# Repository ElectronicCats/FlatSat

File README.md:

# Flatsat 

<p align="center">
    <a href="https://github.com/ElectronicCats/FlatSat/wiki">
        <img src="https://private-user-images.githubusercontent.com/107638696/595693319-c0883c17-046c-4819-b3c2-2ec70a0c5052.png?jwt=eyJ0eXAiOiJKV1QiLCJhbGciOiJIUzI1NiJ9.eyJpc3MiOiJnaXRodWIuY29tIiwiYXVkIjoicmF3LmdpdGh1YnVzZXJjb250ZW50LmNvbSIsImtleSI6ImtleTUiLCJleHAiOjE3OTEyMzc0NjYsIm5iZiI6MTc5MTIzNzE2NiwicGF0aCI6Ii8xMDc2Mzg2OTYvNTk1NjkzMzE5LWMwODgzYzE3LTA0NmMtNDgxOS1iM2MyLTJlYzcwYTBjNTA1Mi5wbmc_WC1BbXotQWxnb3JpdGhtPUFXUzQtSE1BQy1TSEEyNTYmWC1BbXotQ3JlZGVudGlhbD1BS0lBVkNPRFlMU0E1M1BRSzRaQSUyRjIwMjYxMDA1JTJGdXMtZWFzdC0xJTJGczMlMkZhd3M0X3JlcXVlc3QmWC1BbXotRGF0ZT0yMDI2MTAwNVQyMTUyNDZaJlgtQW16LUV4cGlyZXM9MzAwJlgtQW16LVNpZ25hdHVyZT0wM2RjYmU0NjI5OGJjNTY4YjhhNTAxMzIxZWE2ZTU4NDdjMzZmOTUyMDU1MGM0ODgwMjBiM2Y4Zjc5MjgxMDYzJlgtQW16LVNpZ25lZEhlYWRlcnM9aG9zdCZyZXNwb25zZS1jb250ZW50LXR5cGU9aW1hZ2UlMkZwbmcifQ.afATuDfkrx6oh0gf8nJ7T6D2viSOg3LT_uPS4Qk82Y4" width=70%>
    </a>
</p>

<p align=center>

</p>

Flatsat is a hardware based training platform designed to be vulnerable on purpose. It’s built for hackers, engineers, and space enthusiasts who want to dive deep into space-grade systems, learn cybersecurity concepts, and prototype their own payloads.

Flatsat is designed to help you learn and prototype radio systems safely and legally, all while gaining real-world skills in RF communication, signal analysis, and protocol fuzzing.

## What You Can Do With Flatsat
- **Hands-on Learning:** Use Flatsat as the hardware companion to the [**PwnSat**](https://pwnsat.org/) course, with structured lessons on binary exploitation, secure communication, reverse engineering, and space protocols.
- **Hack Real Vulnerabilities:**  Explore and exploit firmware designed to simulate real-world satellite systems and vulnerabilities. It’s a safe playground for learning and discovery.
- **Join the Mission CTF:**  Participate in space-themed capture-the-flag challenges that simulate real satellite operation scenarios.
- **Prototype Your Payloads:**  Use the onboard components to develop and test your own payload logic, radio communication, or telemetry systems before launching bigger projects.

> [!IMPORTANT]
> **This project was created for educational purposes, to teach and learn aerospace cybersecurity. Neither PWNSAT nor Electronic Cats are responsible for how the knowledge, code, or tools hosted in the official repository are used. Use only against hardware, firmware, or signal sources you own or are explicitly authorized to test.**
> 
> Flatsat uses ISM (Industrial, Scientific, and Medical) band frequencies for all RF communication,  typically 433 MHz or 915 MHz, depending on your region. These frequencies are internationally reserved for unlicensed, experimental, and educational use.
>
> This ensures that Flatsat does not interfere with any production space systems, licensed satellites, or critical ground infrastructure.

## Hardware Infrastructure

The infrastructure is designed for **FlatSat** testing, where hardware components are laid out for accessibility and auditing.

| **Component** | **Description**           | **Interface**            |
| ------------- | ------------------------- | ------------------------ |
| **MCU**       | Raspberry Pi RP2040       | Dual Core ARM Cortex-M0+ |
| **Radio 0**   | SX1262 LoRa (Uplink)      | SPI0 / NSS Pin 17        |
| **Radio 1**   | SX1262 LoRa (Downlink)    | SPI0 / NSS Pin 5         |
| **IMU**       | LIS2DH12 Accelerometer    | I2C (SDA 20, SCL 21)     |
| **ENV**       | BME280 Environment Sensor | I2C (SDA 20, SCL 21)     |
| **Status**    | WS2812B NeoPixel          | GPIO 15                  |

##  FlatSat Firmware

The firmware splits tasks across two cores, the system ensures that high-speed data links do not interfere with time-critical radio operations.

The firmware is located in a different repository: https://github.com/ElectronicCats/flatsat-ground-station

The core of the communication system is the [**CCSDS Space Packet Protocol**](https://ccsds.org/Pubs/133x0b2e2.pdf). This allows the spacecraft to route data using **Application Process Identifiers (APIDs)**, enabling modular subsystem addressing.

Modern satellites are no longer isolated systems; they are software-defined assets. The vulnerabilities identified in this firmware mirror historical "anomalies" and documented attacks on orbiting infrastructure.

Since the firmware lacks a Cryptographic Authentication layer, the system is vulnerable to **Command Spoofing**.

An attacker uses a Software Defined Radio (SDR) to capture a legitimate "Telemetry" packet to identify the `SPACECRAFT_ID` and the current `Sequence Count`.
  
This happened in the real world. In 1998, the **ROSAT** (Röntgen Satellite) was allegedly compromised via a ground station breach, where attackers sent commands to point the solar panels directly at the sun, eventually frying the batteries. While that was a network breach, the lack of authentication on the RF link makes this firmware susceptible to the same outcome.

## Technical Documentation and Guides (Wiki)

All deep technical documentation, source analysis, and setup guides have been centralized. If you want to start debugging, or exploiting the platform, please visit the [FlatSat Wiki](https://github.com/ElectronicCats/FlatSat/wiki). The information from the Pwnsat repository has been included in our wiki.

## How to contribute 

[pwnsat.org](https://pwnsat.org/) and [flatsat.org](https://flatsat.org/)
Contributions are welcome!

Please read the document [**Contribution manual**](https://github.com/ElectronicCats/electroniccats-cla/blob/main/electroniccats-contribution-manual.md) which will show you how to contribute your changes to the project.

✨ Thanks to all our [Contributors](https://github.com/ElectronicCats/Flatsat/graphs/contributors)! ✨

See [**_Electronic Cats CLA_**](https://github.com/ElectronicCats/electroniccats-cla/blob/main/electroniccats-cla.md) for more information.

See the [**Community code of conduct**](https://github.com/ElectronicCats/electroniccats-cla/blob/main/electroniccats-community-code-of-conduct.md) for a vision of the community we want to build and what we expect from it.

## License

Electronic Cats invests time and resources providing this open source design, please support Electronic Cats and open-source hardware by purchasing products from Electronic Cats!

Designed by Electronic Cats and PWNSAT.

Hardware released under an CERN Open Hardware Licence v1.2. See the LICENSE_HARDWARE file for more information.

Electronic Cats and PWNSAT is a registered trademark, please do not use if you sell these PCBs.

## Special Thanks
A special thanks to **Alex Lynd**. His support made it possible to kick off the first version of the project, and his contribution remains a fundamental part of PwnSat. His work will always be embedded in what this project has become.

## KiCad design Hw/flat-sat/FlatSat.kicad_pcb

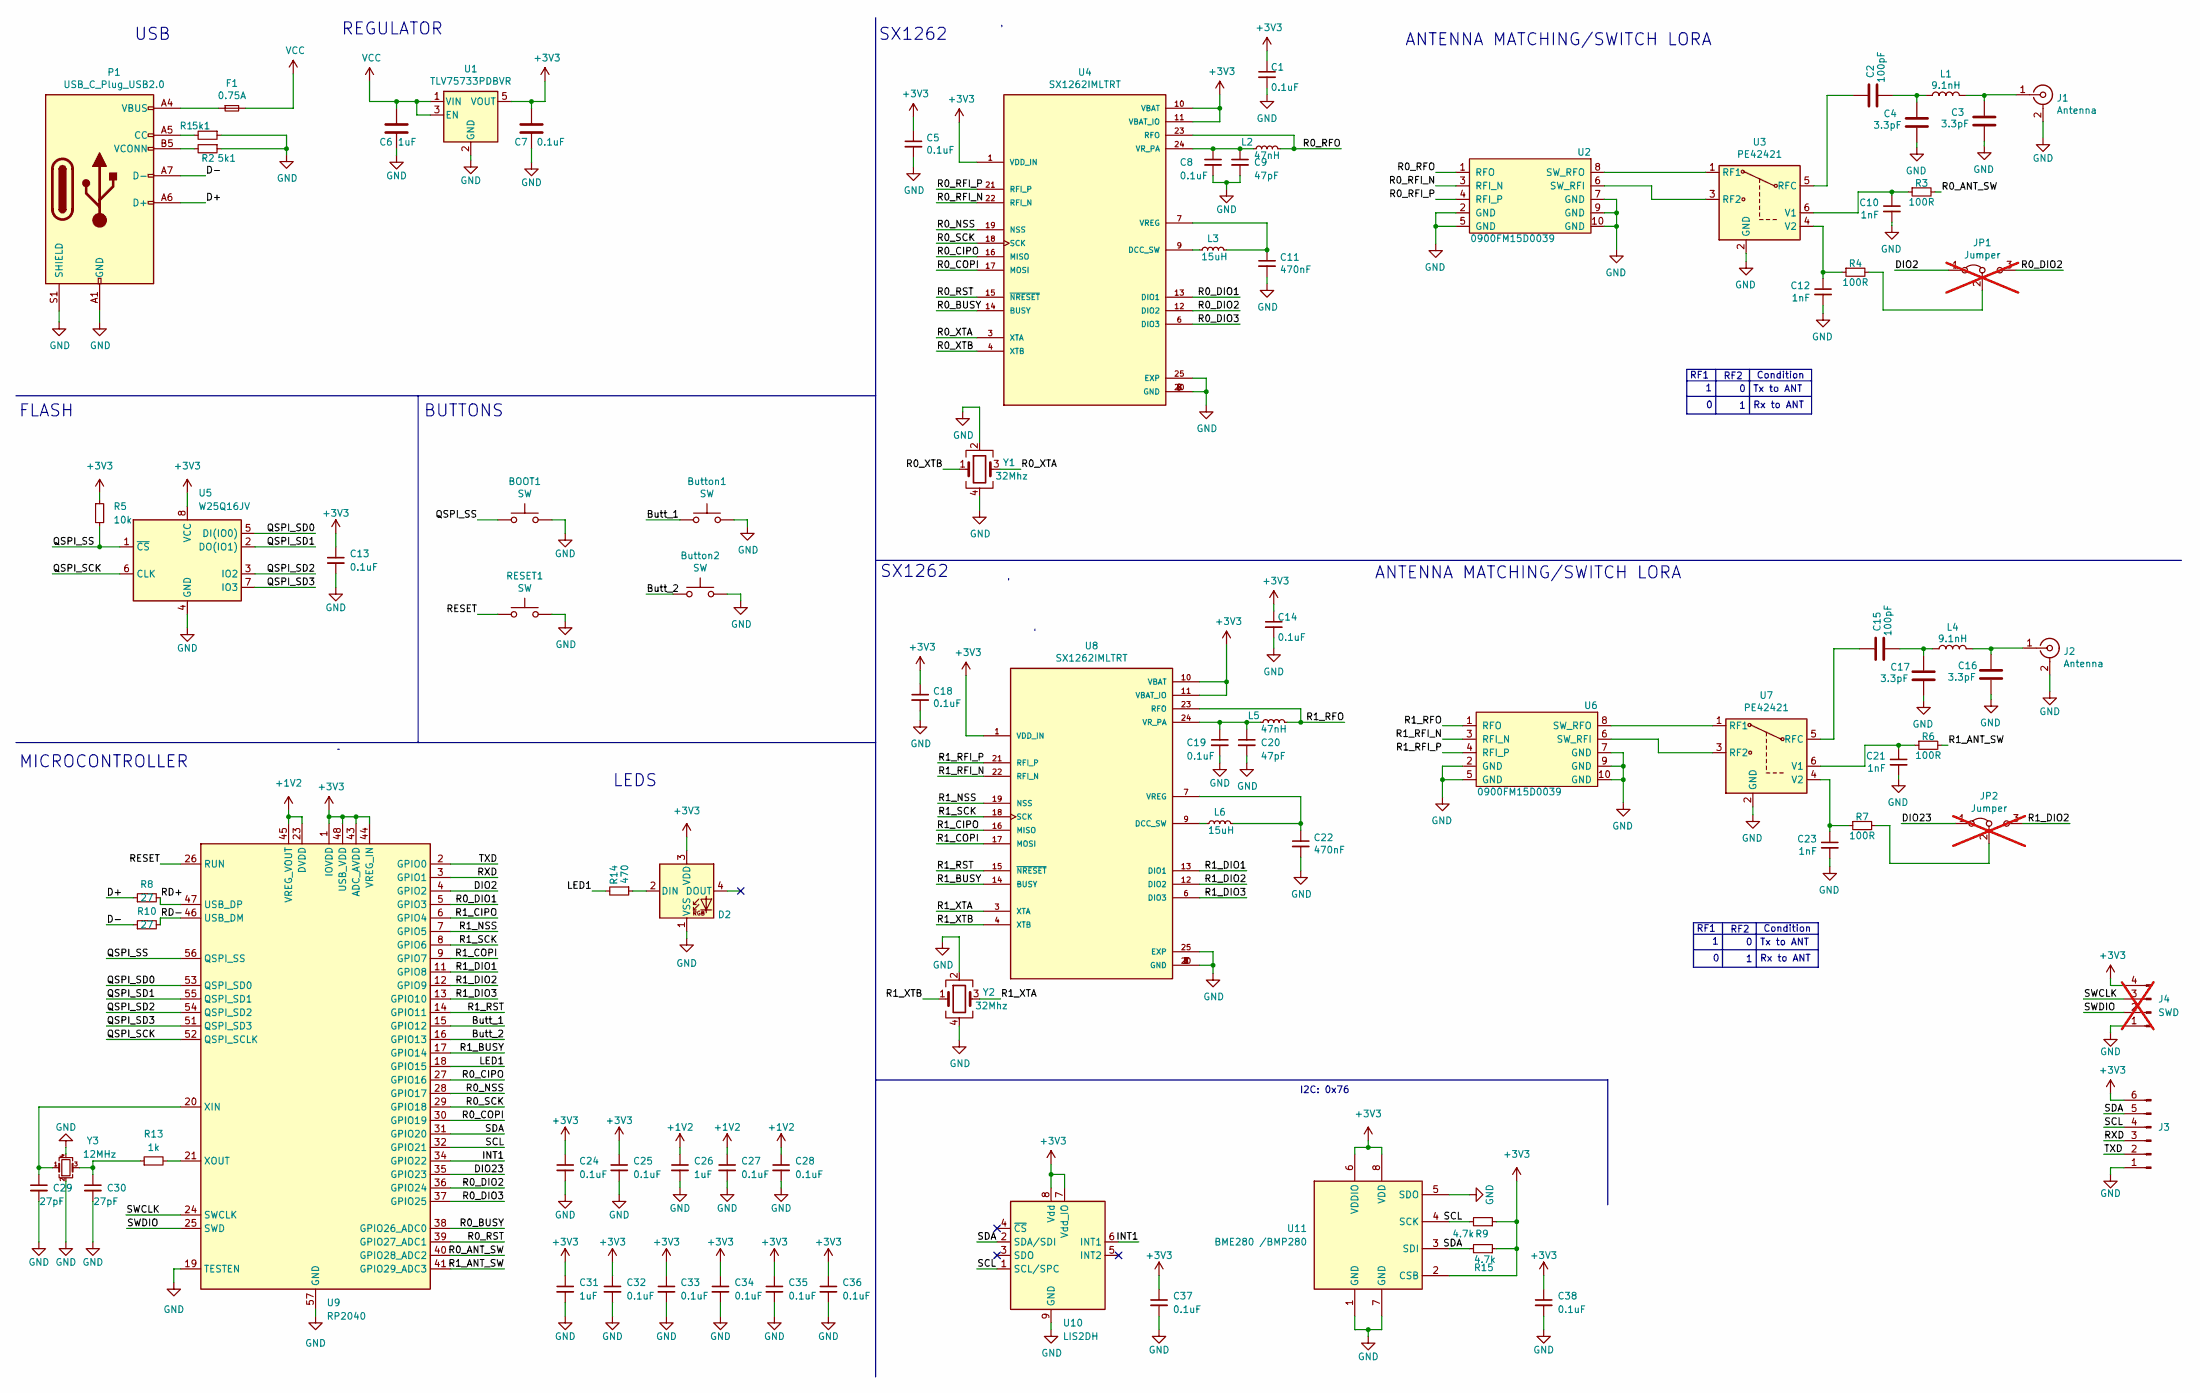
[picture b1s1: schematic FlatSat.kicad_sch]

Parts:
BOOT1: SW; TS1088R02026; LCSC# C455281
Button1, Button2: SW; TS1088R02026; LCSC# C455281
C1, C5, C7, C8, C13, C14, C18, C19, C24, C25, C27, C28, C32, C33, C34, C35, C36, C37, C38: 0.1uF; C_0402_1005Metric; LCSC# C56392
C2, C15: 100pF; C_0402_1005Metric; LCSC# C541374
C3, C4, C16, C17: 3.3pF; C_0402_1005Metric; LCSC# C1565
C6, C26, C31: 1uF; C_0402_1005Metric; LCSC# C52923
C9, C20: 47pF; C_0402_1005Metric; LCSC# C437519
C10, C12, C21, C23: 1nF; C_0402_1005Metric; LCSC# C335530
C11, C22: 470nF; C_0402_1005Metric; LCSC# C47339
C29, C30: 27pF; C_0402_1005Metric; Mouser# 81-GJM1555C1H270FB1D; LCSC# C424826
D2: SK6812MINI; SK6812MINI-HS; LCSC# C2922787
F1: 0.75A; Fuse_0603_1608Metric_Pad1.05x0.95mm_HandSolder; Mouser# 594-MFU0805FF00500P1
J1, J2: Antenna; SMA_EDGE; LCSC# C530661
J3: periphs; PinHeader_1x06_P2.54mm_Vertical
J4: SWD; PinHeader_1x04_P2.54mm_Vertical; not fitted
JP1, JP2: Jumper; SolderJumper-3_P1.3mm_Bridged12_RoundedPad1.0x1.5mm_NumberL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; not fitted
L1, L4: 9.1nH; L_0603_1608Metric; LCSC# C395094
L2, L5: 47nH; L_0603_1608Metric; LCSC# C578001
L3, L6: 15uH; L_0603_1608Metric; LCSC# C57838
P1: USB_C_Plug_USB2.0; C393939; LCSC# C709357
R1, R2: 5k1; R_0402_1005Metric; LCSC# C25905
R3, R4, R6, R7: 100R; R_0402_1005Metric; LCSC# C25076
R5: 10k; R_0402_1005Metric; Mouser# 594-MCS04020D1002BE0; LCSC# C25531
R8, R10: 27; R_0402_1005Metric; Mouser# 755-ESR01MZPF27R0; LCSC# C25100
R9, R15: 4.7k; R_0402_1005Metric; Mouser# 594-MCS04020D1002BE0; LCSC# C25900
R13: 1k; R_0402_1005Metric; Mouser# 594-MCS0402MD1001DE0; LCSC# C11702
R14: 470; R_0402_1005Metric; LCSC# C25117
RESET1: SW; TS1088R02026; LCSC# C455281
U1: TLV75733PDBVR; SOT-23-5; LCSC# C485517
U2, U6: 0900FM15D0039; 0900FM15D0039E; Mouser# 609-0900FM15D0039E
U3, U7: PE42421; SOT-363_SC-70-6; Mouser# 81-PE42421SCAA-Z; LCSC# C470893
U4, U8: SX1262IMLTRT; QFN-24-1EP_4x4mm_P0.5mm_EP2.65x2.65mm; Mouser# 947-SX1262IMLTRT
U5: W25Q16JV; Winbond_USON-8-2EP_3x4mm_P0.8mm_EP0.2x0.8mm; Mouser# 454-W25Q16JVUUIQTR
U9: RP2040; QFN-56-1EP_7x7mm_P0.4mm_EP3.2x3.2mm; LCSC# C2040
U10: LIS2DH; LGA-14_2x2mm_P0.35mm_LayoutBorder3x4y; LCSC# C155670
U11: BME280 /BMP280; Bosch_LGA-8_2.5x2.5mm_P0.65mm_ClockwisePinNumbering; LCSC# C92489
Y1, Y2: 32Mhz; Crystal_SMD_2520-4Pin_2.5x2.0mm; LCSC# C255969
Y3: 12MHz; Crystal_SMD_3225-4Pin_3.2x2.5mm; LCSC# C2848217

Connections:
+1V2: C26.1, C27.1, C28.1, U9.23 (DVDD), U9.45 (VREG_VOUT), U9.50 (DVDD)
+3V3: C1.1, C5.1, C7.2, C13.1, C14.1, C18.1, C24.1, C25.1, C31.1, C32.1, C33.1, C34.1, C35.1, C36.1, C37.1, C38.1, D2.3 (VDD), J3.6, J4.4, R5.1, R9.1, R15.1, U1.5 (VOUT), U4.1 (VDD_IN), U4.10 (VBAT), U4.11 (VBAT_IO), U5.8 (VCC), U8.1 (VDD_IN), U8.10 (VBAT), U8.11 (VBAT_IO), U9.1 (IOVDD), U9.10 (IOVDD), U9.22 (IOVDD), U9.33 (IOVDD), U9.42 (IOVDD), U9.43 (ADC_AVDD), U9.44 (VREG_IN), U9.48 (USB_VDD), U9.49 (IOVDD), U10.7 (Vdd_IO), U10.8 (Vdd), U11.2 (CSB), U11.6 (VDDIO), U11.8 (VDD)
/Butt_1: Button1.1, U9.15 (GPIO12)
/Butt_2: Button2.1, U9.16 (GPIO13)
/D+: P1.A6 (D+), R8.1
/D-: P1.A7 (D-), R10.1
/DIO2: JP1.1 (A), U9.4 (GPIO2)
/DIO23: JP2.1 (A), U9.35 (GPIO23)
/INT1: U9.34 (GPIO22), U10.6 (INT1)
/LED1: R14.2, U9.18 (GPIO15)
/QSPI_SCK: U5.6 (CLK), U9.52 (QSPI_SCLK)
/QSPI_SD0: U5.5 (DI(IO0)), U9.53 (QSPI_SD0)
/QSPI_SD1: U5.2 (DO(IO1)), U9.55 (QSPI_SD1)
/QSPI_SD2: U5.3 (IO2), U9.54 (QSPI_SD2)
/QSPI_SD3: U5.7 (IO3), U9.51 (QSPI_SD3)
/QSPI_SS: BOOT1.1, R5.2, U5.1 (~CS), U9.56 (QSPI_SS)
/R0_ANT_SW: R3.2, U9.40 (GPIO28_ADC2)
/R0_BUSY: U4.14 (BUSY), U9.38 (GPIO26_ADC0)
/R0_CIPO: U4.16 (MISO), U9.27 (GPIO16)
/R0_COPI: U4.17 (MOSI), U9.30 (GPIO19)
/R0_DIO1: U4.13 (DIO1), U9.5 (GPIO3)
/R0_DIO2: JP1.3 (B), U4.12 (DIO2), U9.36 (GPIO24)
/R0_DIO3: U4.6 (DIO3), U9.37 (GPIO25)
/R0_NSS: U4.19 (NSS), U9.28 (GPIO17)
/R0_RFI_N: U2.3 (RFI_N), U4.22 (RFI_N)
/R0_RFI_P: U2.4 (RFI_P), U4.21 (RFI_P)
/R0_RFO: L2.2, U2.1 (RFO), U4.23 (RFO)
/R0_RST: U4.15 (~NRESET), U9.39 (GPIO27_ADC1)
/R0_SCK: U4.18 (SCK), U9.29 (GPIO18)
/R0_XTA: U4.3 (XTA), Y1.3
/R0_XTB: U4.4 (XTB), Y1.1
/R1_ANT_SW: R6.2, U9.41 (GPIO29_ADC3)
/R1_BUSY: U8.14 (BUSY), U9.17 (GPIO14)
/R1_CIPO: U8.16 (MISO), U9.6 (GPIO4)
/R1_COPI: U8.17 (MOSI), U9.9 (GPIO7)
/R1_DIO1: U8.13 (DIO1), U9.11 (GPIO8)
/R1_DIO2: JP2.3 (B), U8.12 (DIO2), U9.12 (GPIO9)
/R1_DIO3: U8.6 (DIO3), U9.13 (GPIO10)
/R1_NSS: U8.19 (NSS), U9.7 (GPIO5)
/R1_RFI_N: U6.3 (RFI_N), U8.22 (RFI_N)
/R1_RFI_P: U6.4 (RFI_P), U8.21 (RFI_P)
/R1_RFO: L5.2, U6.1 (RFO), U8.23 (RFO)
/R1_RST: U8.15 (~NRESET), U9.14 (GPIO11)
/R1_SCK: U8.18 (SCK), U9.8 (GPIO6)
/R1_XTA: U8.3 (XTA), Y2.3
/R1_XTB: U8.4 (XTB), Y2.1
/RD+: R8.2, U9.47 (USB_DP)
/RD-: R10.2, U9.46 (USB_DM)
/RESET: RESET1.1, U9.26 (RUN)
/RXD: J3.3, U9.3 (GPIO1)
/SCL: J3.4, R9.2, U9.32 (GPIO21), U10.1 (SCL/SPC), U11.4 (SCK)
/SDA: J3.5, R15.2, U9.31 (GPIO20), U10.2 (SDA/SDI), U11.3 (SDI)
/SWCLK: J4.3, U9.24 (SWCLK)
/SWDIO: J4.2, U9.25 (SWD)
/TXD: J3.2, U9.2 (GPIO0)
GND: BOOT1.2, Button1.2, Button2.2, C1.2, C3.2, C4.2, C5.2, C6.1, C7.1, C8.2, C9.2, C10.2, C11.2, C12.2, C13.2, C14.2, C16.2, C17.2, C18.2, C19.2, C20.2, C21.2, C22.2, C23.2, C24.2, C25.2, C26.2, C27.2, C28.2, C29.2, C30.2, C31.2, C32.2, C33.2, C34.2, C35.2, C36.2, C37.2, C38.2, D2.1 (VSS), J1.2 (Ext), J2.2 (Ext), J3.1, J4.1, P1.A1 (GND), P1.A12 (GND), P1.B1 (GND), P1.B12 (GND), P1.S1 (SHIELD), R1.1, R2.1, RESET1.2, U1.2 (GND), U2.2 (GND), U2.5 (GND), U2.7 (GND), U2.9 (GND), U2.10 (GND), U3.2 (GND), U4.2 (GND), U4.5 (GND), U4.8 (GND), U4.20 (GND), U4.25 (EXP), U5.4 (GND), U6.2 (GND), U6.5 (GND), U6.7 (GND), U6.9 (GND), U6.10 (GND), U7.2 (GND), U8.2 (GND), U8.5 (GND), U8.8 (GND), U8.20 (GND), U8.25 (EXP), U9.19 (TESTEN), U9.57 (GND), U10.9 (GND), U10.10 (GND), U10.11 (GND), U10.12 (GND), U10.13 (GND), U10.14 (GND), U11.1 (GND), U11.5 (SDO), U11.7 (GND), Y1.2, Y1.4, Y2.2, Y2.4, Y3.2, Y3.4
unnamed: C2.2, C4.1, L1.2
unnamed: C15.2, C17.1, L4.2
unnamed: C30.1, R13.1, Y3.3
unnamed: D2.2 (DIN), R14.1
unnamed: F1.1, P1.A4 (VBUS), P1.A9 (VBUS), P1.B4 (VBUS), P1.B9 (VBUS)
unnamed: C3.1, J1.1 (In), L1.1
unnamed: C16.1, J2.1 (In), L4.1
unnamed: JP1.2 (C), R4.2
unnamed: JP2.2 (C), R7.2
unnamed: P1.A5 (CC), R1.2
unnamed: P1.B5 (VCONN), R2.2
unnamed: U2.6 (SW_RFI), U3.3 (RF2)
unnamed: U2.8 (SW_RFO), U3.1 (RF1)
unnamed: C2.1, U3.5 (RFC)
unnamed: C10.1, R3.1, U3.6 (V1)
unnamed: C12.1, R4.1, U3.4 (V2)
unnamed: L3.1, U4.9 (DCC_SW)
unnamed: C11.1, L3.2, U4.7 (VREG)
unnamed: C8.1, C9.1, L2.1, U4.24 (VR_PA)
unnamed: U6.6 (SW_RFI), U7.3 (RF2)
unnamed: U6.8 (SW_RFO), U7.1 (RF1)
unnamed: C15.1, U7.5 (RFC)
unnamed: C21.1, R6.1, U7.6 (V1)
unnamed: C23.1, R7.1, U7.4 (V2)
unnamed: L6.1, U8.9 (DCC_SW)
unnamed: C22.1, L6.2, U8.7 (VREG)
unnamed: C19.1, C20.1, L5.1, U8.24 (VR_PA)
unnamed: C29.1, U9.20 (XIN), Y3.1
unnamed: R13.2, U9.21 (XOUT)
VCC: C6.2, F1.2, U1.1 (VIN), U1.3 (EN)

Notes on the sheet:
Rx to ANT
I2C: 0x76
Condition
REGULATOR
SX1262
ANTENNA MATCHING/SWITCH LORA
RF1
RF2
FLASH
Tx to ANT
BUTTONS
MICROCONTROLLER
USB
SX1262
LEDS

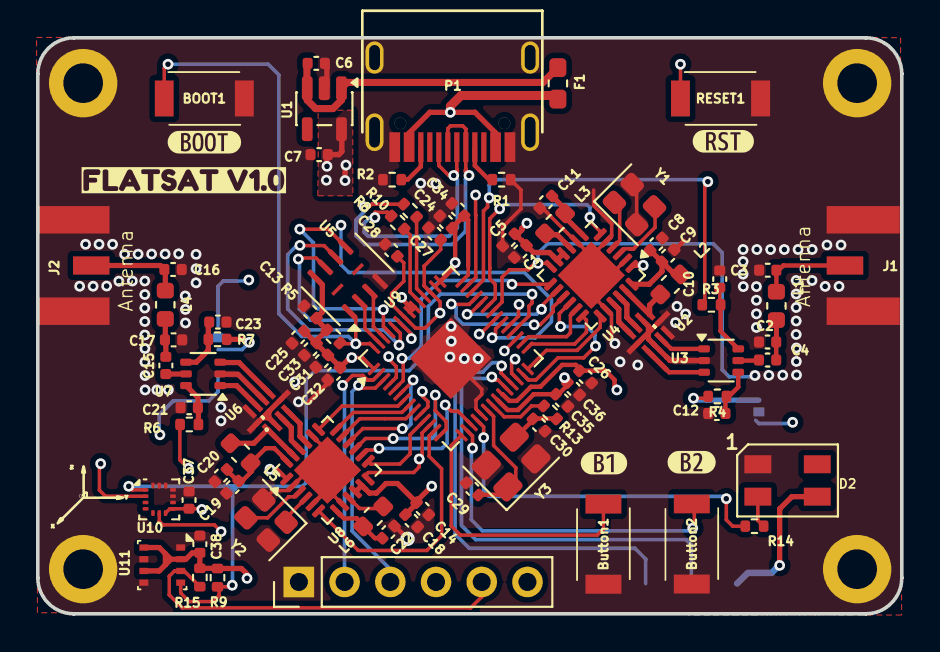
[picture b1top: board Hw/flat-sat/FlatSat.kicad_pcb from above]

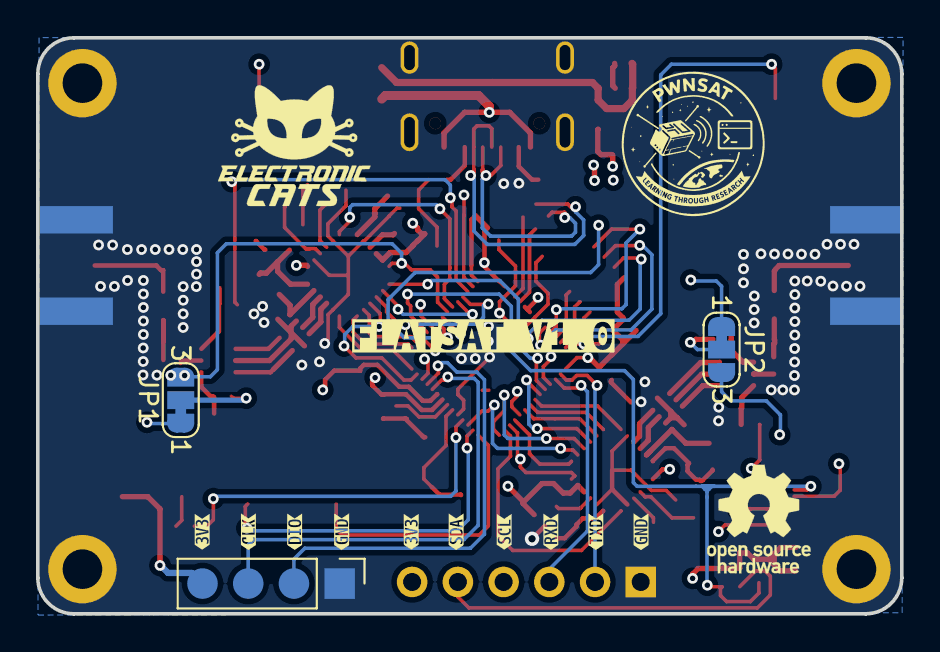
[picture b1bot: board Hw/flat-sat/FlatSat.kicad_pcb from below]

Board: 4 copper layers, 48.0 x 32.0 mm, 100 parts (14 on the bottom side), 86 nets.

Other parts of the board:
kibuzzard-696512BA, kibuzzard-696512BA#2: G***; kibuzzard-696512BA
kibuzzard-696512FB: G***; kibuzzard-696512FB
kibuzzard-6965130C: G***; kibuzzard-6965130C
kibuzzard-6965136B: G***; kibuzzard-6965136B
kibuzzard-69651236: G***; kibuzzard-69651236
kibuzzard-69651254: G***; kibuzzard-69651254
kibuzzard-69651304: G***; kibuzzard-69651304
kibuzzard-69651319: G***; kibuzzard-69651319
kibuzzard-69651321: G***; kibuzzard-69651321
kibuzzard-69651375: G***; kibuzzard-69651375
kibuzzard-69651380: G***; kibuzzard-69651380
kibuzzard-69652909: G***; kibuzzard-69652909
kibuzzard-69652922: G***; kibuzzard-69652922
kibuzzard-69652959: G***; kibuzzard-69652959
kibuzzard-69653048: G***; kibuzzard-69653048

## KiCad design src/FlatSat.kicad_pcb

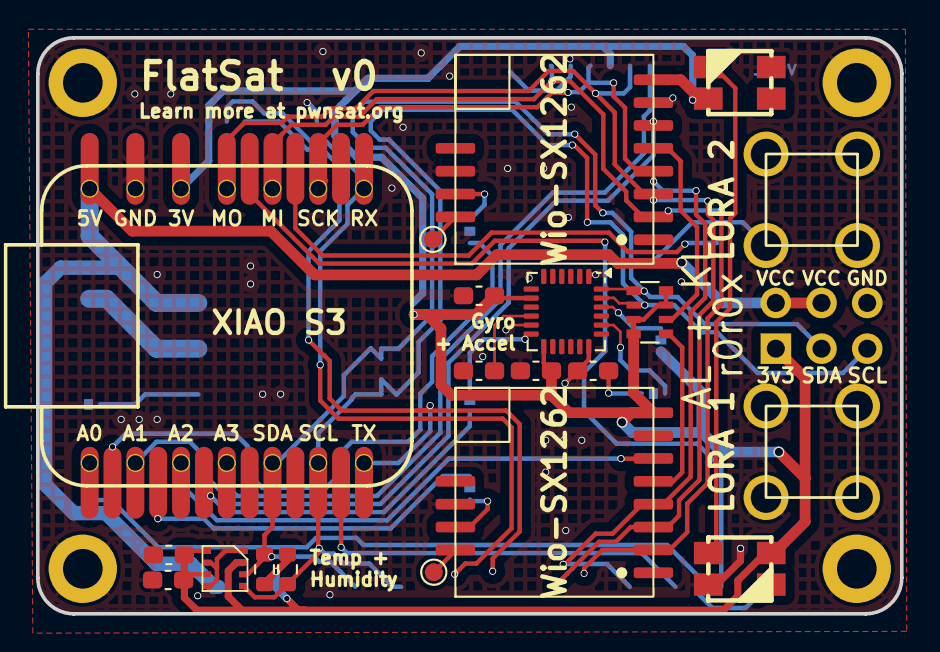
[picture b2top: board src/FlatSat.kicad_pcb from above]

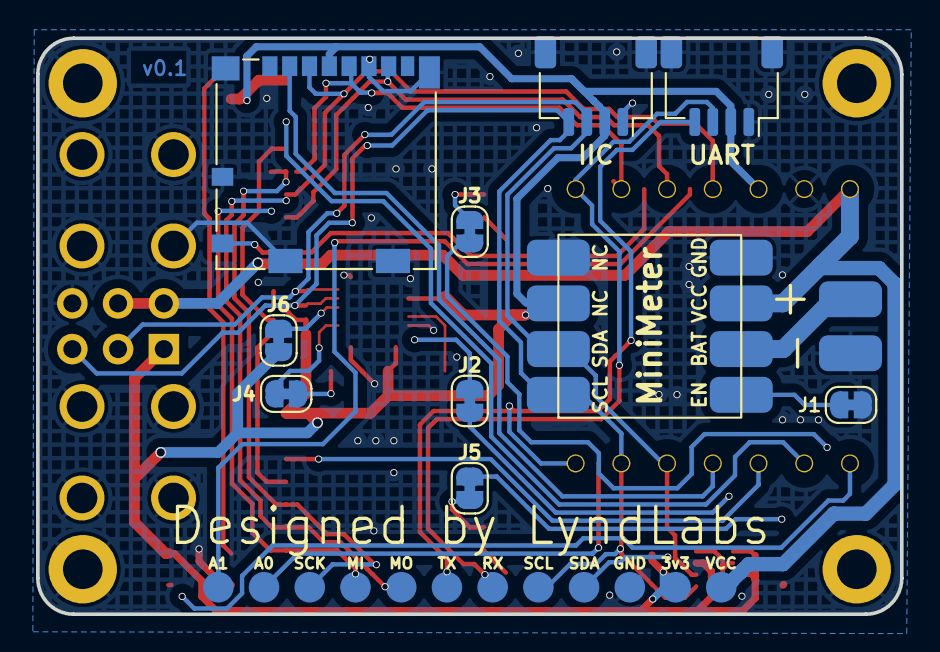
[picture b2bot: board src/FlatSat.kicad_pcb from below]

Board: 2 copper layers, 48.0 x 32.0 mm, 33 parts (12 on the bottom side), 34 nets.

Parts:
AE1, AE2: u.fl to SMA Edge Mount; SMA_Amphenol_901-143_Horizontal
C1, C4, C5: 0.1uf; C_0603_1608Metric_Pad1.08x0.95mm_HandSolder
C2: 2.2uf; C_0603_1608Metric_Pad1.08x0.95mm_HandSolder
C3, C6: 100nF; C_0603_1608Metric_Pad1.08x0.95mm_HandSolder
D1, D2: SK6812MINI; LED_SK6812MINI_PLCC4_3.5x3.5mm_P1.75mm
J1: LiPo; JST_PH_S2B-PH-SM4-TB_1x02-1MP_P2.00mm_Horizontal
J2, J3: Conn_01x04_MountingPin; JST_SH_SM04B-SRSS-TB_1x04-1MP_P1.00mm_Horizontal
J4: Conn_02x03_Odd_Even; PinHeader_2x03_P2.54mm_Vertical
J5: Conn_01x12_Pin; PinHeader_1x12_P2.54mm_Vertical
J7: Micro_SD_Card_Det2; microSD_HC_Molex_104031-0811
JP1, JP2, JP3, JP4, JP5, JP6: SolderJumper_2_Bridged; SolderJumper-2_P1.3mm_Bridged_RoundedPad1.0x1.5mm
R4, R5: 4.7K; R_0603_1608Metric
RN1: 10K; R_Array_Convex_4x0603
TP1, TP2: TestPoint; TestPoint_Pad_D1.0mm
U1: Xiao; XIAO_SMT
U2: MPU-6050 / 6500; InvenSense_QFN-24_4x4mm_P0.5mm
U3: BME280 /BMP280; Bosch_LGA-8_2.5x2.5mm_P0.65mm_ClockwisePinNumbering
U4: MiniMeter
U5, U6: Wio-SX1262

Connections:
+3V3: C3.1, C4.1, C5.1, C6.1, D1.4 (VDD), D2.4 (VDD), J2.2, J3.2, J4.1, J5.2, J7.4 (VDD), JP6.2 (B), R4.2, R5.1, RN1.3 (R3.1), RN1.4 (R4.1), RN1.7 (R2.2), RN1.8 (R1.2), U1.12 (3V3), U2.8 (VLOGIC), U2.13 (VDD), U3.2 (CSB), U3.6 (VDDIO), U3.8 (VDD), U4.2 (3V3), U5.8 (VCC), U6.8 (VCC)
A0: J5.11, U1.20 (D16)
A1: J5.12, U1.23 (D17)
BUSY1: JP3.2 (B), U1.15 (D11)
BUSY2: JP5.2 (B), U1.16 (D12)
CS1: U1.2 (D1), U5.6 (NSS)
CS2: U1.3 (D2), U6.6 (NSS)
GND: AE1.1, AE2.1, C1.2, C2.2, C3.2, C4.2, C5.2, C6.2, D1.2 (VSS), D2.2 (VSS), J1.1, J2.1, J2.MP (MountPin), J3.1, J3.MP (MountPin), J4.6, J5.3, J7.6 (VSS), J7.9 (DET_B), J7.11 (SHIELD), JP1.1 (A), U1.13 (GND), U2.1 (CLKIN), U2.11 (FSYNC), U2.18 (GND), U3.1 (GND), U3.5 (SDO), U3.7 (GND), U4.1 (GND), U4.5 (GND), U5.7 (GND), U5.10 (GND), U6.7 (GND), U6.10 (GND)
INT: JP2.2 (B), U1.17 (D13)
LED: D1.3 (DIN), U1.1 (D0)
MCU_RX: J2.3, J5.6, U1.8 (RX)
MCU_TX: J2.4, J5.7, U1.7 (TX)
MISO: J5.9, J7.7 (DAT0), U1.10 (MISO), U5.2 (MISO), U6.2 (MISO)
MOSI: J5.8, J7.3 (CMD), U1.11 (MOSI), U5.3 (MOSI), U6.3 (MOSI)
NCS: JP6.1 (A), U2.22 (NCS)
unnamed: D1.1 (DOUT), D2.3 (DIN)
unnamed: JP1.2 (B), U4.8 (EN)
unnamed: JP2.1 (A), U2.12 (INT)
unnamed: JP3.1 (A), U5.11 (BUSY)
unnamed: JP4.1 (A), U2.20 (CPOUT)
unnamed: C2.1, JP4.2 (B)
unnamed: JP5.1 (A), U6.11 (BUSY)
unnamed: RN1.6 (R3.2), U5.5 (RST)
unnamed: RN1.5 (R4.2), U6.5 (RST)
unnamed: C1.1, U2.10 (REGOUT)
unnamed: TP1.1, U5.12 (DI01)
unnamed: TP2.1, U6.12 (DI01)
SCK: J5.10, J7.5 (CLK), U1.9 (SCK), U5.4 (CLK), U6.4 (CLK)
SCL: J3.4, J4.5, J5.5, R4.1, RN1.2 (R2.1), U1.6 (SCL), U2.23 (SCL), U3.4 (SCK), U4.4 (SCL)
SDA: J3.3, J4.3, J5.4, R5.2, RN1.1 (R1.1), U1.5 (SDA), U2.24 (SDA), U3.3 (SDI), U4.3 (SDA)
SD_CS: J7.2 (DAT3/CD), U1.4 (D3)
SD_DT: J7.10 (DET_A), U1.22 (D18)
VBAT: J1.2, U4.7 (VBAT)
VCC: J4.2, J4.4, J5.1, U1.14 (5V), U4.6 (VCC)

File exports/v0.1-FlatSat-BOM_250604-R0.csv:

Designator,Value,Footprint,Datasheet,LCSC,Qty
"C1,C3,C4,C5,C6",100nF,603,~,C14663,5
C2,2.2uf,603,~, C57895,1
"D1,D2",SK6812MINI,3535,,C7423117,2
"J2,J3",JST SH ,SM04B,~,C160404,2
J7,MicroSD,,https://www.molex.com/en-us/products/part-detail/1040310811,C585350,1
"R4,R5",4.7K,603,~, C99782,2
RN1,10K,Resistor_SMD:R_Array_Convex_4x0603,~,C110924,1
U2,MPU-6500,Sensor_Motion:InvenSense_QFN-24_4x4mm_P0.5mm,https://invensense.tdk.com/wp-content/uploads/2015/02/MPU-60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, C50278,1
U3,BME280,Package_LGA:Bosch_LGA-8_2.5x2.5mm_P0.65mm_ClockwisePinNumbering,https://www.bosch-sensortec.com/media/boschsensortec/downloa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,C92489,1
"U5,U6",WIO-SX1262,,https://www.seeedstudio.com/Wio-SX1262-Wireless-Module-p-5981.html,NA,2

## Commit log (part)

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2025-07-23 update routing for MPU6050 + fix traces + jumpers
2025-07-23 update v0.2 gerber + pnp file
2025-08-04 feat: Add new cases
2026-01-05 Re-structure repository add new kicad project
2026-01-05 Remove previous layout, update gitignore
2026-01-05 feat(Hw):Update_sch
    Pending review
2026-01-06 fet(Hw):Init_floorplan_Update_LCSC#
2026-01-06 feat(Hw):Update_Pcb_And
    Pending_some_pins
2026-01-07 feat(Hw):Update_Route
    Pending_Neo
2026-01-08 feat(Hw):Mounting_Holes_Added
2026-01-08 feat(Hw):3D_Model_Added_First_Route
2026-01-08 Add CERN Open Hardware Licence v1.2
    Added the CERN Open Hardware Licence v1.2 to the project.
2026-01-08 Revise README with project details and contribution info
    Updated README to include detailed project description, collaboration guidelines, and contribution instructions.
2026-01-09 Expand README with Flatsat features and components
    Added detailed sections on capabilities and components of Flatsat.
2026-01-09 Update README with communication bands information
    Added information about communication bands used in Flatsat.
2026-01-09 feat(Hw):Update_PCB_Change_Buttons
    Pending_Check_LIS2DH
2026-01-12 feat(Hw):Logos_Added
2026-01-12 feate(Hw):Updated_logos
2026-01-12 feat(Hw):Update_Mounting_Holes_And_a_C
2026-01-12 feat(Hw):LC_Layout_Updated
2026-01-12 fix(Hw):Labels_Updated
2026-01-13 feat(Hw):Update_BoM
2026-01-14 Fix(Hw): update RF floorplan
2026-01-15 fix(Hw):Floorplan_Updated
2026-01-19 fix ground plane 4 layers
